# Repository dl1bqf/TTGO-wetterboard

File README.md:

TTGO_wetterboard
Hucke Pack Leiterplatte für das TTGO32 Beam ab Version 1.0 zur Implementation von Wetter Sensoren

implementiert ist das DHT11/22,BMP280 oder BME280, UV Sensor VELM6070,Blitzsensor AS3935 Modul.
Ein 128x 96 OLED Display dient zur Anzeige der Messwerte. 2 Tasten dienen der Menu Steuerung.
Eine NF Buchse kann zur Ein /Ausgabe externe Geräte benutzt werden. 

Installation 

Löte als erstes auf der Boardoberseite die Kondensatoren C1 und C2 Smd 0805 22nf ein.
Löte R1 , R2 und R3 SMD 0805 10 Kohm ein.
Löte die Schottky Dioden D1,D2,D3. Achtung !! Polung beachten Anode zeigt zum Header hin.
Löte am Header J3 eine 3 polig Stiftleiste von rechts beginnend ein. Lasse 4 Lötaugen aus 
 und löte eine 6 polige Stiftleiste ab Pin 8 ein. 
Löte an J4 ein 13 polige Stiftleiste ein. Alle Stiftleisten werden von unten gesteckt und oben gelötet
Bereite das Display vor.Löte ein 4 polige Stiftleiste am Display an, falls noch nicht vorhanden. Achtung !!
das Display muss am linken Stift VDD haben am 2. von links GND. Es gibt auch Displays wo es anders herum ist.
Ziehe anschließend das schwarze Distanzstück von der Stiftleiste so das nur noch 4 blanke Stifte am Display sind.
Isoliere die beiden Bohrlöcher vom Display rechts und links von der Stiftleiste an der Displayunterseite.
Stecke das Display von oben durch das Wetterboard und verlöte es von unten. Das Display ist dabei soweit wie möglich
nach unten zu drücken.
Nehme ein Multimeter, messe auf den Pins VDD GND auf Durchgang. Ist kein Durchgang vorhanden kann ein erster Test gemacht werden.
Stecke das Weatherboard auf das TTGO32 Beam und schalte das TTGO ein. Jetzt müsste auf dem Display der Startvorgang zu sehen 
sein. Schalte das TTGO aus und ziehe das Wetterboard ab.
Löte jetzt noch die beiden Tasten SW1 und SW2 auf, und anschließend das DHT22 Modul auf der Oberseite, wie auf der Platine gezeichnet.
Löte danach noch die beiden Module BME280 und das UV-A Sensormodul VEML6070 auf. Ziehe auch auch hier bei beiden Modulen das schwarze
Distanzstück von der Stiftleiste ab so das die die Module Plan auf den Wetterboard aufliegen.
Wer die Ausgabe der empfangenen LoRa Station in Morsetelegrafie haben möchte kann noch an J5 einen Miniaturlautsprecher anlöten. Diesen
kann man leicht in alten Smartphones oder DECT Telefonen  ausbauen.
 
Alle anderen Bauteile sind nicht zu bestücken und dienen nur zukünftige Entwicklung und sind noch in Arbeit

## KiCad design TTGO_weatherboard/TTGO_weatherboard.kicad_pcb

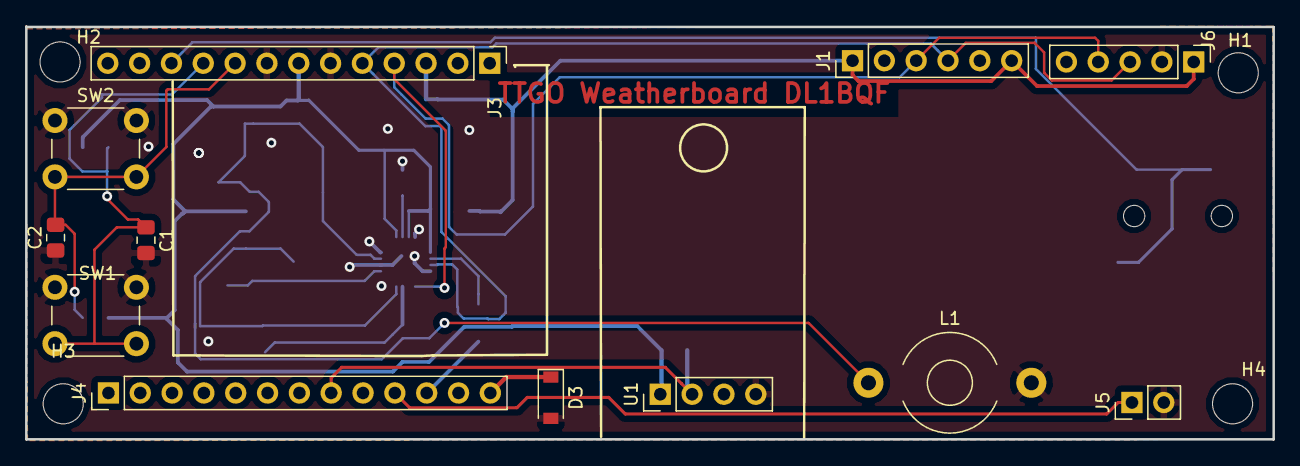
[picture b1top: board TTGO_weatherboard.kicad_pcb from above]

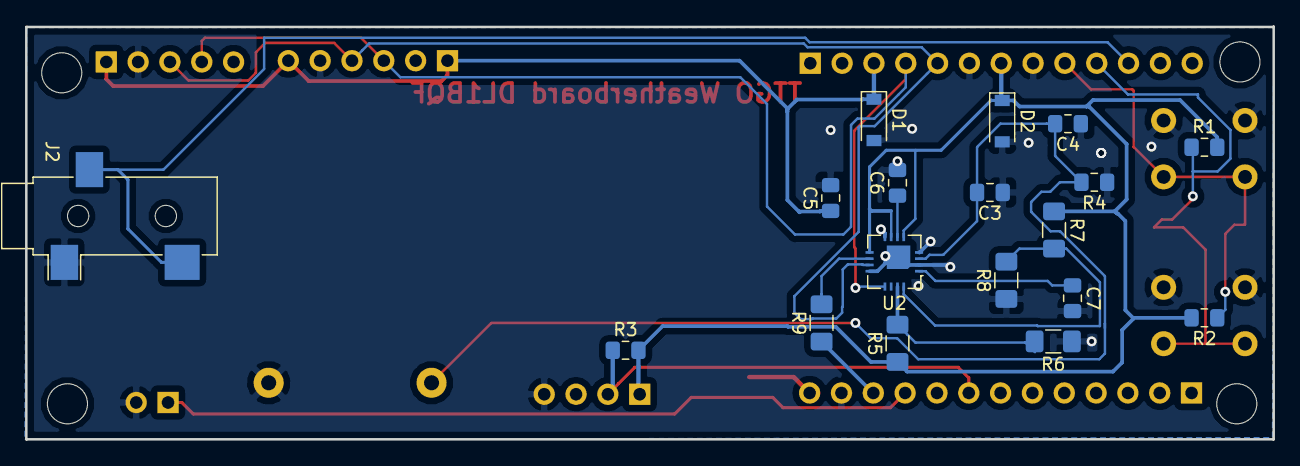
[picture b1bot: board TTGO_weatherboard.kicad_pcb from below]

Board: 2 copper layers, 99.5 x 33.0 mm, 34 parts (18 on the bottom side), 17 nets.

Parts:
C1, C2: 22 nf; C_0805_2012Metric_Pad1.15x1.40mm_HandSolder
C3: 670; C_0805_2012Metric_Pad1.15x1.40mm_HandSolder
C4: 270; C_0805_2012Metric_Pad1.15x1.40mm_HandSolder
C5, C6, C7: 1 µF; C_0805_2012Metric_Pad1.15x1.40mm_HandSolder
D1, D2, D3: PMEG6010; D_SOD-123
H1, H2, H3: MountingHole; MountingHole_3.2mm_M3
H4: m; MountingHole_3.2mm_M3
J1: BME/BMP280; PinHeader_1x06_P2.54mm_Vertical
J2: AudioJack3; Jack_3.5mm_CUI_SJ-3523-SMT_Horizontal
J3, J4: PinHeader_1x13_P2.54mm_Vertical
J5: buzzer; PinHeader_1x02_P2.54mm_Vertical
J6: VEML6070; PinHeader_1x05_P2.54mm_Vertical
L1: 100 µH; L_Toroid_Horizontal_D7.8mm_P13.00mm_Diameter9-5mm_Amidon-T30
R1, R2, R3, R4: 10 K; R_0805_2012Metric_Pad1.15x1.40mm_HandSolder
R5, R6, R7, R8, R9: 0; R_1206_3216Metric_Pad1.42x1.75mm_HandSolder
SW1, SW2: SW_Push; SW_PUSH_6mm
U1: DHT11/22; PinHeader_1x04_P2.54mm_Vertical
U2: AS3935; as3935_MLPQ_16_4x4mm_Pitch0.5mm

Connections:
+3V3: C5.1, D1.1, D2.1, J1.1, J1.6, J3.3, J3.7, J6.1, R1.2, R2.2, R3.2, R5.1, R7.1, U1.1, U2.5, U2.7, U2.9
+5V: D3.1, J4.13
GND: C1.2, C2.1, C3.1, C4.1, C5.2, C6.2, C7.2, D1.2, D2.2, D3.2, J1.5, J2.S, J3.6, J3.8, J4.12, J5.2, J6.2, L1.2, R4.1, R6.1, R8.1, SW1.1, SW2.1, U1.4, U2.2, U2.4, U2.8, U2.12, U2.17
unnamed: C1.1, J3.10, R1.1, SW1.2
unnamed: C2.2, J3.9, R2.1, SW2.2
unnamed: C3.2, C4.2, L1.1, R4.2, U2.3
unnamed: C6.1, U2.6
unnamed: C7.1, U2.1
unnamed: J1.3, J3.4, J6.4, U2.13
unnamed: J1.4, J3.5, J6.3, U2.11
unnamed: J2.R, J2.T, J3.11
unnamed: J4.8, R3.1, U1.2
unnamed: J4.10, J5.1
unnamed: J4.11, R9.1
unnamed: R5.2, R6.2, U2.15
unnamed: R7.2, R8.2, U2.16
unnamed: R9.2, U2.10
